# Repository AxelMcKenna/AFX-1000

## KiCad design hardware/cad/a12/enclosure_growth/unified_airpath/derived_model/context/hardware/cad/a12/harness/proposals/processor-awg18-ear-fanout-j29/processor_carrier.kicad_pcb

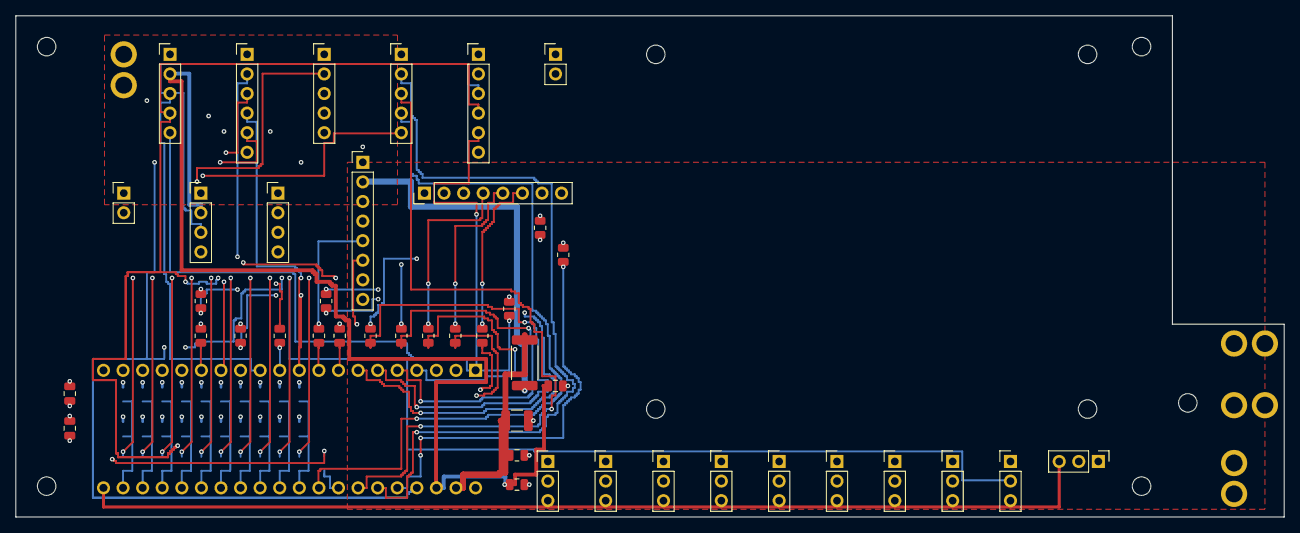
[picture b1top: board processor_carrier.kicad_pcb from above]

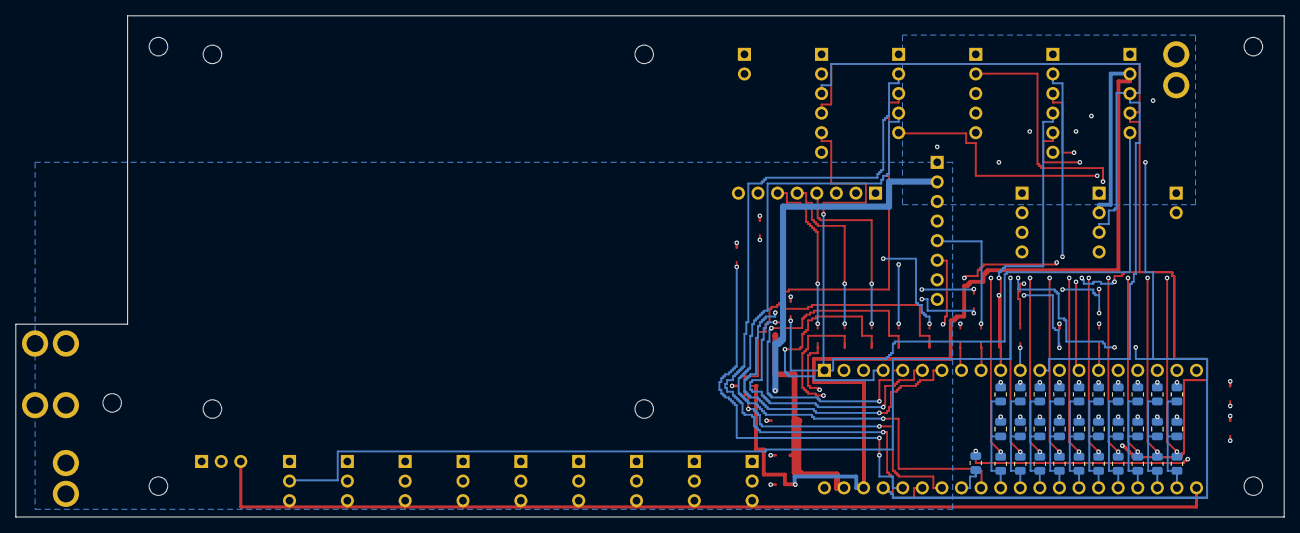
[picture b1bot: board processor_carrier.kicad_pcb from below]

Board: 4 copper layers, 164.5 x 65.0 mm, 88 parts (31 on the bottom side), 61 nets.

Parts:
C1: 22uF 25V X7R; C_1210_3225Metric
C2, C4, C6, C11, C12, C13, C14, C15, C16, C17, C18, C19, C20: 100nF 16V X7R; C_0805_2012Metric
C3: 1uF 16V X7R; C_0805_2012Metric
C5: 4.7uF 16V X7R; C_0805_2012Metric
H1, H2, H3, H4, H9: M2_CLEARANCE; M2_Insert_Clearance
H5, H6, H7, H8: M2_CLEARANCE; M2_Daughter
J1, J13, J14, J15: Alpha6715_AWG18_DIRECT_SOLDER_PROPOSAL; AWG18_Solder_2x1_P4mm_D2p2
J2, J4, J5: Header5; PinHeader_1x05_P2.54mm_Vertical
J3, J6: Header6; PinHeader_1x06_P2.54mm_Vertical
J7, J8: Header2; PinHeader_1x02_P2.54mm_Vertical
J9, J10: Header4; PinHeader_1x04_P2.54mm_Vertical
J11, J12: Header8; PinHeader_1x08_P2.54mm_Vertical
J20, J21, J22, J23, J24, J25, J26, J27, J28, J29: Header3; PinHeader_1x03_P2.54mm_Vertical
R1: 0.47R 1% 1W; R_2512_6332Metric
R2: 10k 1%; R_0805_2012Metric
R3, R4, R5, R6: 100k 1%; R_0805_2012Metric
R10, R11, R12, R13, R14, R15, R16, R17, R18, R19, R20: 33R 1%; R_0805_2012Metric
R31, R32, R33, R34, R35, R36, R37, R38, R39, R40: 1k 1%; R_0805_2012Metric
R41, R42, R43, R44, R45, R46, R47, R48, R49, R50: 1M 1%; R_0805_2012Metric
U1: DaisySeed3; Seed3_Socket40

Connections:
/5V_DIG: J1.1, J11.2, J13.1, J14.1, J15.1, R1.1
/ADC_DATA: J5.4, U1.32
/AGND: C1.2, C2.2, C3.2, C4.2, C5.2, C6.2, C11.2, C12.2, C13.2, C14.2, C15.2, C16.2, C17.2, C18.2, C19.2, C20.2, J1.2, J2.1, J3.1, J4.1, J5.1, J6.1, J7.1, J8.1, J9.1, J10.1, J11.1, J11.8, J12.1, J13.2, J14.2, J15.2, J20.1, J21.1, J22.1, J23.1, J24.1, J25.1, J26.1, J27.1, J28.1, J29.1, R3.2, R4.2, R5.2, R6.2, R41.2, R42.2, R43.2, R44.2, R45.2, R46.2, R47.2, R48.2, R49.2, R50.2, U1.20, U1.40
/ANALOG_OK: J4.4, J6.6
/ARMED: J3.5, R5.1, U1.37
/BCLK: J5.2, U1.35
/BYPASS_SENSE: J3.6, J4.3
/CODEC_RUN: J2.5, J6.5, R6.1, U1.1
/DAC_DATA: J5.5, R14.2
/DAC_DATA_SRC: R14.1, U1.33
/GAIN_REQ: J3.4, R4.1, U1.10
/HEARTBEAT: J3.2, U1.14
/INPUT_READY: J4.5, J7.2
/LED_BLANK: J11.7, R2.1, R13.2
/LED_BLANK_SRC: R13.1, U1.15
/LED_MOSI: J11.4, R12.2
/LED_MOSI_SRC: R12.1, U1.11
/LED_SCK: J11.5, R11.2
/LED_SCK_SRC: R11.1, U1.9
/LED_XLAT: J11.6, R10.2
/LED_XLAT_SRC: R10.1, U1.8
/MCU_PERMIT: J3.3, R3.1, U1.36
/MODE_SEND_RETURN: J4.2, J8.2
/POT_ADC_00: C11.1, R31.2, R41.1, U1.22
/POT_ADC_01: C12.1, R32.2, R42.1, U1.23
/POT_ADC_02: C13.1, R33.2, R43.1, U1.24
/POT_ADC_03: C14.1, R34.2, R44.1, U1.25
/POT_ADC_04: C15.1, R35.2, R45.1, U1.26
/POT_ADC_05: C16.1, R36.2, R46.1, U1.27
/POT_ADC_06: C17.1, R37.2, R47.1, U1.28
/POT_ADC_07: C18.1, R38.2, R48.1, U1.29
/POT_ADC_08: C19.1, R39.2, R49.1, U1.30
/POT_ADC_09: C20.1, R40.2, R50.1, U1.31
/POT_RAW_00: J20.2, R31.1
/POT_RAW_01: J21.2, R32.1
/POT_RAW_02: J22.2, R33.1
/POT_RAW_03: J23.2, R34.1
/POT_RAW_04: J24.2, R35.1
/POT_RAW_05: J25.2, R36.1
/POT_RAW_06: J26.2, R37.1
/POT_RAW_07: J27.2, R38.1
/POT_RAW_08: J28.2, R39.1
/POT_RAW_09: J29.2, R40.1
/SCL: J2.3, J6.3, J9.3, J10.3, U1.12
/SDA: J2.4, J6.4, J9.4, J10.4, U1.13
/SDMMC_CLK: J12.8, R20.2
/SDMMC_CLK_SRC: R20.1, U1.7
/SDMMC_CMD: J12.7, R19.2
/SDMMC_CMD_SRC: R19.1, U1.6
/SDMMC_D0: J12.3, R15.2
/SDMMC_D0_SRC: R15.1, U1.5
/SDMMC_D1: J12.4, R16.2
/SDMMC_D1_SRC: R16.1, U1.4
/SDMMC_D2: J12.5, R17.2
/SDMMC_D2_SRC: R17.1, U1.3
/SDMMC_D3: J12.6, R18.2
/SDMMC_D3_SRC: R18.1, U1.2
/SEED_VIN: C1.1, C2.1, R1.2, U1.39
/V3V3_ANALOG: C3.1, C4.1, J20.3, J21.3, J22.3, J23.3, J24.3, J25.3, J26.3, J27.3, J28.3, J29.3, U1.21
/V3V3_IO: C5.1, C6.1, J2.2, J6.2, J9.2, J10.2, J11.3, J12.2, R2.2, U1.38
/WS: J5.3, U1.34

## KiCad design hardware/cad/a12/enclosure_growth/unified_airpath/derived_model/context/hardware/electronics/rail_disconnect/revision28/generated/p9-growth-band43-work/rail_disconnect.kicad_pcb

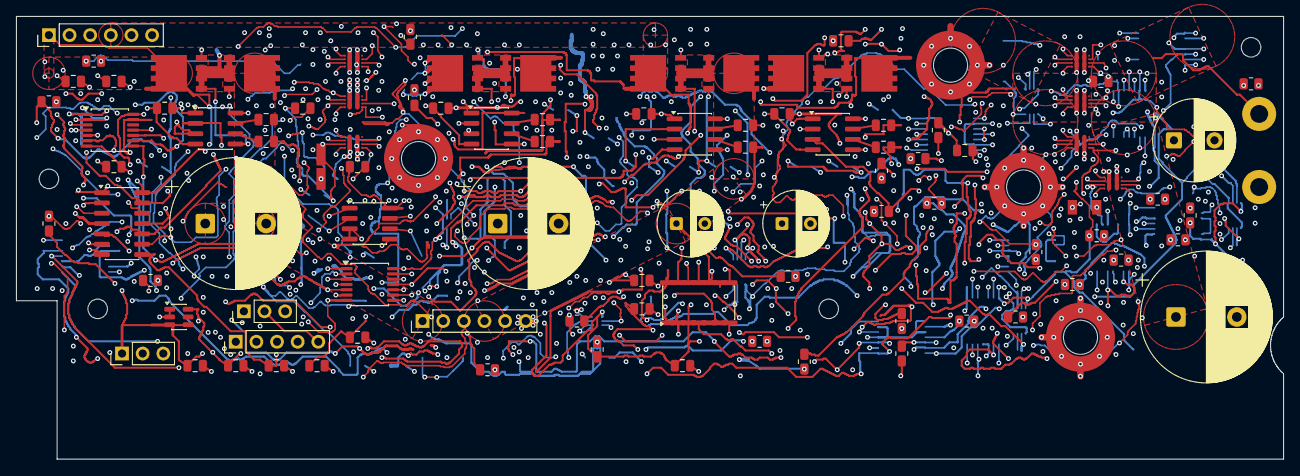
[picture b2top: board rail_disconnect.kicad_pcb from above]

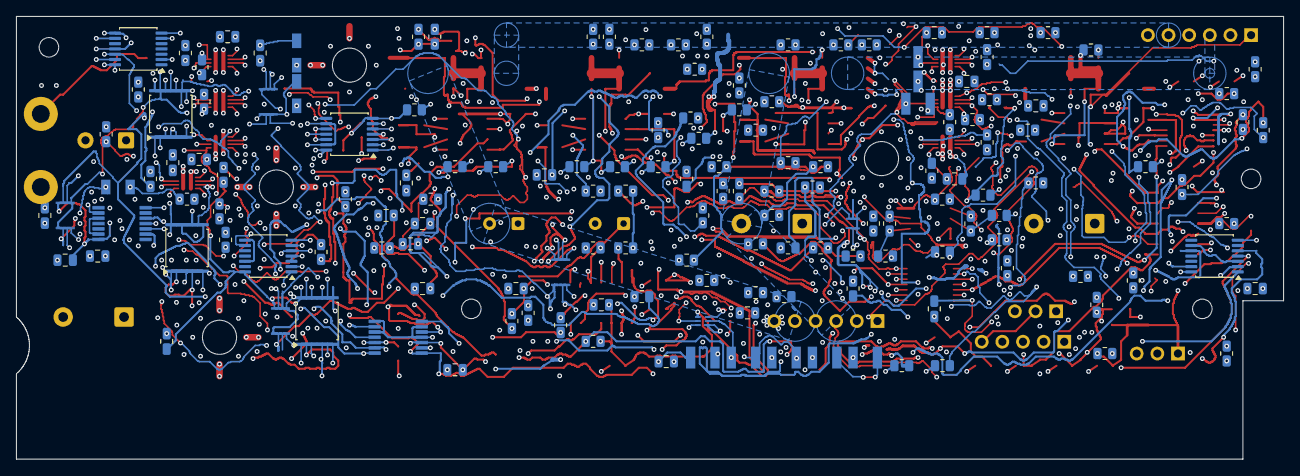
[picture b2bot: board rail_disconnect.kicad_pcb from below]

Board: 6 copper layers, 156.0 x 54.5 mm, 255 parts (151 on the bottom side), 174 nets.

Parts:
C1, C5, C9, C13, C17, C21, C25, C29, C34, C35, C36, C37, C57, C58, C59, C66, C67, C68, C69, C70, C71, C72, C73, C74, C75, C76, C77: 100nF 16V X7R; C_0805_2012Metric
C2, C3, C6, C7, C10, C11, C14, C15: 10pF 100V C0G 5%; C_0805_2012Metric
C4, C8: 1500uF 35V electrolytic 20% EEUFR1V152S; CP_Radial_D16.0mm_P7.50mm
C12, C16: 220uF 35V electrolytic 20% EEUFR1V221; CP_Radial_D8.0mm_P3.50mm
C20: 1500uF 16V electrolytic 20% EEUFR1C152; CP_Radial_D10.0mm_P5.00mm
C24: 4700uF 16V electrolytic 20% EEUFR1C472; CP_Radial_D16.0mm_P7.50mm
C26: 1uF 16V X7R; C_0805_2012Metric
C27, C28, C30, C31, C32, C33, C53, C54, C55, C56: 100pF 50V C0G 5%; C_0805_2012Metric
C38: 10uF 16V X7R; C_0805_2012Metric
C39, C41, C49, C61, C62, C63, C64, C65: 100nF 50V C0G 5% C1210C104J5GACTU; KEMET_C1210_LevelB
C40, C42, C44, C46, C48, C50, C52: 1uF 50V X7R; C_0805_2012Metric
C43, C45, C47, C51: 47nF 50V C0G 5% C1206C473J5GACTU; KEMET_C1206_LevelB
C60: 10nF 50V C0G 5%; C_0805_2012Metric
H1, H2, H3, H4: M2_CLEARANCE; M2_Clearance
J1, J3: Header6; PinHeader_1x06_P2.54mm_Vertical
J4: Alpha3079_AWG14_DIG_FORCE; AWG14_Force_2x1_P9mm_Engineering
J5, J6: Header3; PinHeader_1x03_P2.54mm_Vertical
J7, J8, J10, J11: 7466003R; 7466003R_M3_SMT_Annulus_NPTH
J9: E28 CONTROL; PinHeader_1x05_P2.54mm_Vertical
Q1, Q2, Q3, Q4, Q5, Q6, Q7, Q8: CSD18540Q5B; CSD18540Q5B_TI_Q5B
R1, R9, R17, R25: 22 1%; R_0805_2012Metric
R2, R10, R18, R26, R60, R63, R68, R71, R76, R81, R86, R91: 20M 1%; R_0805_2012Metric
R3, R5, R11, R13, R19, R21, R27, R29, R61, R64, R69, R72, R77, R82, R87, R92, R93: 10k 1%; R_0805_2012Metric
R4, R12, R20, R28, R98, R102, R106, R110, R114, R118, R122: 100 1%; R_0805_2012Metric
R6, R7, R14, R15, R22, R23, R30, R31: 15k 1%; R_0805_2012Metric
R8, R16, R24, R32, R40, R48: 47k 1%; R_0805_2012Metric
R49: 150k 0.01% 5ppm; R_0805_2012Metric
R50: 6.2k 0.01% 5ppm; R_0805_2012Metric
R51, R54, R58, R59, R62, R66, R67, R70, R74, R75, R79, R80, R84, R85, R89, R90, R94, R124, R127, R130, R133: 10k 0.01% 5ppm; R_0805_2012Metric
R52, R55: 1k 1%; R_0805_2012Metric
R53: 100k 0.01% 5ppm; R_0805_2012Metric
R56: 143k 0.01% 5ppm; R_0805_2012Metric
R57: 3.3k 0.01% 5ppm; R_0805_2012Metric
R65: 90.9k 0.01% 5ppm; R_0805_2012Metric
R73, R78: 31.6k 0.01% 5ppm; R_0805_2012Metric
R83: 12.4k 0.01% 5ppm; R_0805_2012Metric
R88: 7.5k 0.01% 5ppm; R_0805_2012Metric
R95, R99, R103, R107, R111, R115, R119, R125, R128, R131, R134, R136, R141: 10k; R_0805_2012Metric
R96, R100, R104, R108, R112, R116, R120, R140: 47k; R_0805_2012Metric
R97, R101, R117: 2.43k 0.1%; R_0805_2012Metric
R105, R109, R113, R121: 604 0.1%; R_0805_2012Metric
R123, R126, R129, R132: 28.7k 0.01% 5ppm; R_0805_2012Metric
R135: 100k; R_0805_2012Metric
R137: 11.1k 0.1%; R_0805_2012Metric
R138: 39.2 0.1%; R_0805_2012Metric
R139: 10k 0.1%; R_0805_2012Metric
R142: 15k; R_0805_2012Metric
U1, U2, U3, U4: SI8751AB-ISR; SOIC-8_3.9x4.9mm_P1.27mm
U7: REF35125QDBVR; SOT-23-6
U8: OPA2333AID; SOIC-8_3.9x4.9mm_P1.27mm
U9, U10: TLV1824DR; SOIC-14_3.9x8.7mm_P1.27mm
U11, U12, U24, U25, U26, U27: SN74LVC08APWR; TSSOP-14_4.4x5mm_P0.65mm
U13, U14, U15, U16, U17, U32, U33: TPS259482LYWP; TPS259482L_YWP0012A
U18: TLV1824PWR; TLV1824_PW0014A
U19, U20: TPS389001DSET; TPS389001_DSE0006A
U21, U22: SN74LVC02APWR; TSSOP-14_4.4x5mm_P0.65mm
U23: SN74LVC32APWR; TSSOP-14_4.4x5mm_P0.65mm
U28: SN74LVC14APWR; SN74LVC14A_PW0014A
U29, U30, U31, U34: SN74AUP2G08DCUR; SN74AUP2G08_DCU0008A

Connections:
/5V_DIG: C24.1, J4.1, R48.1, R132.1, U15.6, U15.11, U16.6, U16.11, U17.6, U17.11, U33.6, U33.11
/5V_DIG_OV_OK: R81.1, R82.2, U10.1, U11.10
/5V_DIG_OV_REF: R80.2, R81.2, U10.7
/5V_DIG_OV_SENSE: C33.1, R78.2, R79.1, U10.6
/5V_DIG_SRC: C44.1, C46.1, C48.1, C52.1, J11.1, R78.1, R126.1, U15.5, U15.12, U16.5, U16.12, U17.5, U17.12, U33.5, U33.12
/AGND: C1.2, C4.2, C5.2, C8.1, C9.2, C12.2, C13.2, C16.1, C17.2, C20.2, C21.2, C24.2, C25.2, C26.2, C27.2, C28.2, C29.2, C30.2, C31.2, C32.2, C33.2, C34.2, C35.2, C36.2, C37.2, C38.2, C39.2, C40.2, C41.2, C42.2, C43.2, C44.2, C45.2, C46.2, C47.2, C48.2, C49.2, C50.2, C51.2, C52.2, C53.2, C54.2, C55.2, C56.2, C57.2, C58.2, C59.2, C60.2, C61.2, C62.2, C63.2, C64.2, C65.2, C66.2, C67.2, C68.2, C69.2, C70.2, C71.2, C72.2, C73.2, C74.2, C75.2, C76.2, C77.2, J1.2, J3.2, J4.2, J5.2, J6.1, J7.1, J8.1, J9.1, R3.2, R5.2, R8.2, R11.2, R13.2, R16.2, R19.2, R21.2, R24.2, R27.2, R29.2, R32.2, R40.2, R48.2, R58.2, R66.2, R74.2, R79.2, R84.2, R89.2, R93.2, R94.2, R96.2, R97.2, R100.2, R101.2, R104.2, R105.2, R108.2, R109.2, R112.2, R113.2, R116.2, R117.2, R120.2, R121.2, R124.2, R127.2, R130.2, R133.2, R139.2, R140.2, R141.2, R142.2, U1.4, U2.4, U3.4, U4.4, U7.1, U7.2, U8.3, U8.4, U8.5, U9.12, U10.12, U11.7, U12.7, U13.2, U13.4, U13.8, U14.2, U14.4, U14.8, U15.2, U15.4, U15.8, U16.2, U16.4, U16.8, U17.2, U17.4, U17.8, U18.12, U19.2, U20.2, U21.7, U22.7, U22.9, U22.12, U23.7, U24.7, U25.4, U25.5, U25.7, U26.7, U27.7, U28.7, U29.4, U30.4, U31.4, U32.2, U32.4, U32.8, U33.2, U33.4, U33.8, U34.4
/ALL_RAILS_ALLOW: U12.11, U21.2, U29.1
/ANA_OUTPUT_OK: R131.2, U18.14, U24.4
/ANA_PG0: R95.1, U13.3, U31.2
/ANA_PG1: R99.1, U14.3, U34.6
/ANA_PG2: R115.1, U26.10, U32.3
/ANA_SOURCE_OK: R125.2, U18.2, U24.1
/DIG_OUTPUT_OK: R134.2, U18.13, U24.5
/DIG_PG0: R103.1, U15.3, U29.6
/DIG_PG1: R107.1, U16.3, U30.2
/DIG_PG2: R111.1, U17.3, U34.2
/DIG_PG3: R119.1, U26.9, U30.6, U33.3
/DIG_SOURCE_OK: R128.2, U18.1, U24.2
/E28_ALL_CHANNELS_READY: U26.8, U26.12
/E28_ANA_0_DVDT: R98.1, U13.7
/E28_ANA_0_DVDT_CAP: C39.1, R98.2
/E28_ANA_0_ILM: R97.1, U13.9
/E28_ANA_1_DVDT: R102.1, U14.7
/E28_ANA_1_DVDT_CAP: C41.1, R102.2
/E28_ANA_1_ILM: R101.1, U14.9
/E28_ANA_2_DVDT: R118.1, U32.7
/E28_ANA_2_DVDT_CAP: C49.1, R118.2
/E28_ANA_2_ILM: R117.1, U32.9
/E28_ANA_ENABLE: R96.1, U13.1, U30.3
/E28_ANA_FOLLOW: R100.1, U14.1, U31.7
/E28_ANA_FOLLOW2: R116.1, U32.1, U34.3
/E28_ANA_OUT_SENSE: C55.1, R129.2, R130.1, U18.9
/E28_ANA_SRC_SENSE: C53.1, R123.2, R124.1, U18.5
/E28_ARMED: U21.3, U21.4, U25.9
/E28_ARM_BAR: U21.1, U21.6
/E28_AUX_CT: C60.1, U19.5
/E28_AUX_DIV: R137.2, R138.1
/E28_AUX_RESET_N: R135.1, U19.6, U31.5
/E28_AUX_SENSE: R138.2, R139.1, U19.1
/E28_AUX_VALID: U24.13, U28.3, U29.2, U31.3
/E28_DIG_0_DVDT: R106.1, U15.7
/E28_DIG_0_DVDT_CAP: C43.1, R106.2
/E28_DIG_0_ILM: R105.1, U15.9
/E28_DIG_1_DVDT: R110.1, U16.7
/E28_DIG_1_DVDT_CAP: C45.1, R110.2
/E28_DIG_1_ILM: R109.1, U16.9
/E28_DIG_2_DVDT: R114.1, U17.7
/E28_DIG_2_DVDT_CAP: C47.1, R114.2
/E28_DIG_2_ILM: R113.1, U17.9
/E28_DIG_3_DVDT: R122.1, U33.7
/E28_DIG_3_DVDT_CAP: C51.1, R122.2
/E28_DIG_3_ILM: R121.1, U33.9
/E28_DIG_FOLLOW1: R108.1, U16.1, U29.3
/E28_DIG_FOLLOW2: R112.1, U17.1, U30.7
/E28_DIG_FOLLOW3: R120.1, U33.1, U34.7
/E28_DIG_OUT_SENSE: C56.1, R132.2, R133.1, U18.11
/E28_DIG_SRC_SENSE: C54.1, R126.2, R127.1, U18.7
/E28_FAULT: J9.4, U21.9, U21.13, U23.5, U28.5
/E28_FAULT_A: U23.8, U23.12
/E28_FAULT_ANY: U23.11, U25.10
/E28_FAULT_BAR: U21.10, U21.12
/E28_FAULT_SET: U21.8, U25.8
/E28_MASTER_ENABLE: J6.2, J9.5, R4.1, R12.1, R20.1, R28.1, R104.1, R141.1, U15.1, U20.1, U20.3, U25.13, U27.2, U29.5, U29.7, U30.1, U30.5, U31.1, U34.1, U34.5
/E28_NORMAL_OK: U22.8, U27.8
/E28_NORMAL_PRE: U24.8, U27.9
/E28_NOT_AUX: U23.2, U28.4
/E28_NOT_FAULT: U27.13, U28.6
/E28_NOT_NORMAL_OK: U22.10, U23.9
/E28_NOT_OUT_READY: U22.13, U26.2, U26.5
/E28_NOT_RUN: U23.1, U28.2, U28.9
/E28_NOT_SOURCE_READY: U28.10, U28.13
/E28_OUTPUT_PERMISSION: U26.11, U27.1
/E28_OUTPUT_READY: J9.3, U27.3
/E28_OUT_ARMED: U22.3, U22.4, U26.1
/E28_OUT_ARM_BAR: U22.1, U22.6
/E28_OUT_READY: U22.11, U24.6, U25.12, U26.13
/E28_OUT_UV_FAULT: U23.10, U26.3
/E28_OUT_VALID_ACTIVE: U22.2, U25.11
/E28_RESET: U21.5, U21.11, U23.3, U23.4
/E28_RESET_OUT: U22.5, U23.6
/E28_RUN_AND_SOURCE: U24.12, U27.6
/E28_RUN_LOGIC: U27.4, U28.8
/E28_SAFE_REQUEST: R140.1, U12.13, U27.11
/E28_SAFE_STAGE: U25.3, U27.12
/E28_SOURCE_READY: U24.3, U24.9, U25.2
/E28_SOURCE_READY_LOGIC: U27.5, U27.10, U28.12
/E28_TIMEOUT: R136.1, U20.6, U26.4
/E28_TIMEOUT_CT: C61.1, C62.1, C63.1, C64.1, C65.1, U20.5
/E28_TIMEOUT_FAULT: U23.13, U26.6
/E28_USER_AUX: U24.11, U25.1
/N12: C16.2, J3.5, Q8.3, R31.1, R32.1
/N12_ALLOW: R28.2, R29.1, U4.3
/N12_COMMON: Q7.1, Q8.1, R26.2, U4.5
/N12_DRIVE: R25.1, U4.8
/N12_GATE: Q7.2, Q8.2, R25.2, R26.1
/N12_INV: R54.1, R55.1, U8.7
/N12_MCAP1: C14.2, U4.7
/N12_MCAP1_LIMIT: C14.1, R30.2
/N12_MCAP2: C15.2, U4.6
/N12_MCAP2_LIMIT: C15.1, R31.2
/N12_OV_OK: R71.1, R72.2, U9.13, U11.5
/N12_OV_REF: R70.2, R71.2, U9.11
/N12_OV_SENSE: C28.1, R55.2, U9.10
/N12_SRC: J1.5, Q7.3, R30.1, R53.1
/N12_SUM: R53.2, R54.2, U8.6
/N12_TT: R27.1, U4.2
/N19: C8.2, J3.3, Q4.3, R15.1, R16.1
/N19_ALLOW: R12.2, R13.1, U2.3
/N19_COMMON: Q3.1, Q4.1, R10.2, U2.5
/N19_DRIVE: R9.1, U2.8
/N19_GATE: Q3.2, Q4.2, R9.2, R10.1
/N19_INPUT_MID: R49.2, R50.1
/N19_INV: R51.1, R52.1, U8.1
/N19_MCAP1: C6.2, U2.7
/N19_MCAP1_LIMIT: C6.1, R14.2
/N19_MCAP2: C7.2, U2.6
/N19_MCAP2_LIMIT: C7.1, R15.2
/N19_OV_OK: R63.1, R64.2, U9.1, U11.2
/N19_OV_REF: R62.2, R63.2, U9.7
/N19_OV_SENSE: C27.1, R52.2, U9.6
/N19_SRC: J1.3, Q3.3, R14.1, R49.1
/N19_SUM: R50.2, R51.2, U8.2
/N19_TT: R11.1, U2.2
/OK_5: U11.8, U12.4
/OK_12: U11.6, U12.2
/OK_19: U11.3, U12.1
/OK_ALL_OV: U12.8, U12.12, U24.10
/OK_ANALOG: U12.3, U12.9
/OK_AUXILIARY: U12.6, U12.10
/OK_REF: U11.11, U12.5
/P03_SOURCES_READY: J9.2, R142.1, U28.11
/P12: C12.1, J3.4, Q6.3, R23.1, R24.1
/P12_ALLOW: R20.2, R21.1, U3.3
/P12_COMMON: Q5.1, Q6.1, R18.2, U3.5
/P12_DRIVE: R17.1, U3.8
/P12_GATE: Q5.2, Q6.2, R17.2, R18.1
/P12_MCAP1: C10.2, U3.7
/P12_MCAP1_LIMIT: C10.1, R22.2
/P12_MCAP2: C11.2, U3.6
/P12_MCAP2_LIMIT: C11.1, R23.2
/P12_OV_OK: R68.1, R69.2, U9.14, U11.4
/P12_OV_REF: R67.2, R68.2, U9.9
/P12_OV_SENSE: C31.1, R65.2, R66.1, U9.8
/P12_SRC: J1.4, Q5.3, R22.1, R65.1
/P12_TT: R19.1, U3.2
/P19: C4.1, J3.1, Q2.3, R7.1, R8.1
/P19_ALLOW: R4.2, R5.1, U1.3
/P19_COMMON: Q1.1, Q2.1, R2.2, U1.5
/P19_DRIVE: R1.1, U1.8
/P19_GATE: Q1.2, Q2.2, R1.2, R2.1
/P19_MCAP1: C2.2, U1.7
/P19_MCAP1_LIMIT: C2.1, R6.2
/P19_MCAP2: C3.2, U1.6
/P19_MCAP2_LIMIT: C3.1, R7.2
/P19_OV_OK: R60.1, R61.2, U9.2, U11.1
/P19_OV_REF: R59.2, R60.2, U9.5
/P19_OV_SENSE: C30.1, R57.2, R58.1, U9.4
/P19_SENSE_MID: R56.2, R57.1
/P19_SRC: J1.1, Q1.3, R6.1, R56.1
/P19_TT: R3.1, U1.2
/POWER_RUN: J5.3, R93.1, U28.1
/PROTECT_REF: C26.1, J6.3, R59.1, R62.1, R67.1, R70.1, R75.1, R80.1, R85.1, R94.1, U7.6, U10.10, U18.4, U18.6, U18.8, U18.10
/REF_HIGH_AUX: R88.2, R89.1, R90.1
/REF_HIGH_OK: R91.1, R92.2, U10.13, U11.13
/REF_HIGH_POSITIVE: R90.2, R91.2, U10.11
/REF_LOW_AUX: R83.2, R84.1, U10.8
/REF_LOW_OK: R86.1, R87.2, U10.14, U11.12
/REF_LOW_POSITIVE: R85.2, R86.2, U10.9
/V2V5_AUX: C1.1, C5.1, C9.1, C13.1, C17.1, C21.1, C25.1, C29.1, C34.1, C35.1, C36.1, C37.1, C38.1, C57.1, C58.1, C59.1, C66.1, C67.1, C68.1, C69.1, C70.1, C71.1, C72.1, C73.1, C74.1, C75.1, C76.1, C77.1, J5.1, R61.1, R64.1, R69.1, R72.1, R77.1, R82.1, R83.1, R87.1, R88.1, R92.1, R95.2, R99.2, R103.2, R107.2, R111.2, R115.2, R119.2, R125.1, R128.1, R131.1, R134.1, R135.2, R136.2, R137.1, U1.1, U2.1, U3.1, U4.1, U7.3, U7.4, U8.8, U9.3, U10.3, U11.14, U12.14, U18.3, U19.3, U19.4, U20.4, U21.14, U22.14, U23.14, U24.14, U25.14, U26.14, U27.14, U28.14, U29.8, U30.8, U31.6, U31.8, U34.8
/V5_REG: C20.1, J3.6, R40.1, R129.1, U13.6, U13.11, U14.6, U14.11, U32.6, U32.11
/V5_REG_OV_OK: R76.1, R77.2, U10.2, U11.9
/V5_REG_OV_REF: R75.2, R76.2, U10.5
/V5_REG_OV_SENSE: C32.1, R73.2, R74.1, U10.4
/V5_REG_SRC: C40.1, C42.1, C50.1, J1.6, J10.1, R73.1, R123.1, U13.5, U13.12, U14.5, U14.12, U32.5, U32.12
